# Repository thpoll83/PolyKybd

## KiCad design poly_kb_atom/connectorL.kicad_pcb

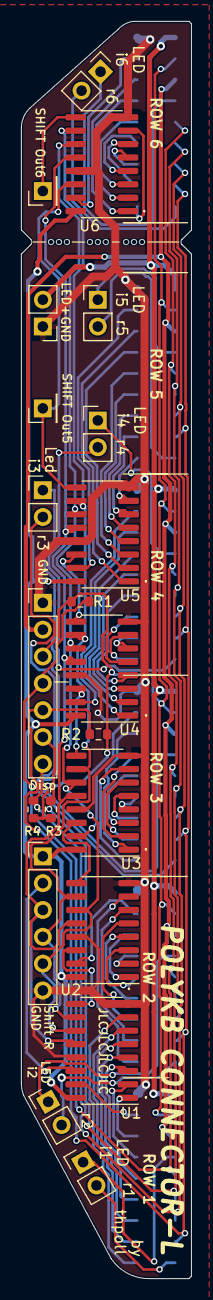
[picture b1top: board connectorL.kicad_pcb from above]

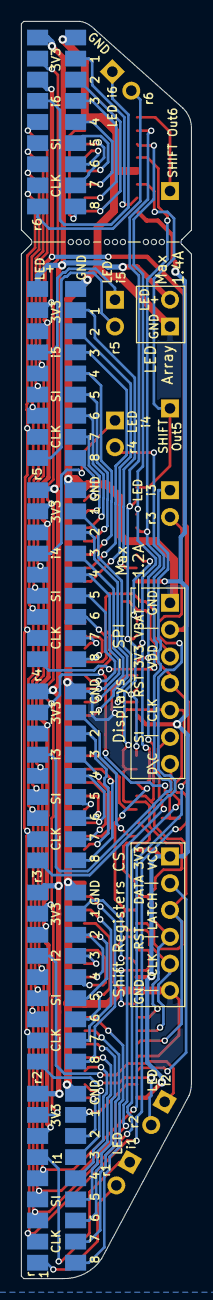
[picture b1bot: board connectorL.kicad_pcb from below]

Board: 2 copper layers, 16.1 x 119.0 mm, 36 parts (12 on the bottom side), 79 nets.

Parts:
J1, J2, J3, J4, J5, J6, J7, J8, J9, J10, J11, J12: Conn_01x09; AtomConnect2
J13: Conn_01x07; PinHeader_1x07_P2.54mm_Vertical
J14: Conn_01x06; PinHeader_1x06_P2.54mm_Vertical
J15, J17: Conn_01x01; PinHeader_1x01_P2.54mm_Vertical
J16, J21, J22, J23, J24, J25, J26: Conn_01x02; PinHeader_1x02_P2.54mm_Vertical
R1, R2, R3, R4: 1M; R_0603_1608Metric
U1, U2, U3, U4, U5, U6: 74HCT595; SOIC-16_3.9x9.9mm_P1.27mm
mouse-bite-2mm-slot, mouse-bite-2mm-slot#2, mouse-bite-2mm-slot#3: VAL**; mouse-bite-3x

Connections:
1: J1.2, U1.15
2: J1.3, U1.1
3: J1.4, U1.2
4: J1.5, U1.3
5: J1.6, U1.4
6: J1.7, U1.5
7: J1.8, U1.6
8: J1.9, U1.7
9: J3.2, U2.15
10: J3.3, U2.1
11: J3.4, U2.2
12: J3.5, U2.3
13: J3.6, U2.4
14: J3.7, U2.5
15: J3.8, U2.6
16: J3.9, U2.7
17: J5.2, U3.15
18: J5.3, U3.1
19: J5.4, U3.2
20: J5.5, U3.3
21: J5.6, U3.4
22: J5.7, U3.5
23: J5.8, U3.6
24: J5.9, U3.7
25: J7.2, U4.15
26: J7.3, U4.1
27: J7.4, U4.2
28: J7.5, U4.3
29: J7.6, U4.4
30: J7.7, U4.5
31: J7.8, U4.6
32: J7.9, U4.7
33: J9.2, U5.15
34: J9.3, U5.1
35: J9.4, U5.2
36: J9.5, U5.3
37: J9.6, U5.4
38: J9.7, U5.5
39: J9.8, U5.6
40: J9.9, U5.7
41: J11.2, U6.15
42: J11.3, U6.1
43: J11.4, U6.2
44: J11.5, U6.3
45: J11.6, U6.4
46: J11.7, U6.5
47: J11.8, U6.6
48: J11.9, U6.7
+3V3: J14.1, U1.16, U2.16, U3.16, U4.16, U5.16, U6.16
CLK: J2.8, J4.8, J6.8, J8.8, J10.8, J12.8, J13.5, R2.2
D\C: J2.7, J4.7, J6.7, J8.7, J10.7, J12.7, J13.7, R4.2
GND: J1.1, J3.1, J5.1, J7.1, J9.1, J11.1, J13.1, J14.6, J16.1, U1.8, U1.13, U2.8, U2.13, U3.8, U3.13, U4.8, U4.13, U5.8, U5.13, U6.8, U6.13
LedIn1: J2.4, J21.1
LedIn2: J4.4, J22.1
LedIn3: J6.4, J23.1
LedIn4: J8.4, J24.1
LedIn5: J10.4, J25.1
LedIn6: J12.4, J26.1
unnamed: U1.9, U2.14
unnamed: U2.9, U3.14
unnamed: U3.9, U4.14
unnamed: U4.9, U5.14
RST: J2.5, J4.5, J6.5, J8.5, J10.5, J12.5, J13.4, R1.2
SHIFTR_AOUT: J17.1, U5.9, U6.14
SHIFTR_CLK: J14.5, U1.11, U2.11, U3.11, U4.11, U5.11, U6.11
SHIFTR_DATA: J14.2, U1.14
SHIFTR_LATCH_CLK: J14.3, U1.12, U2.12, U3.12, U4.12, U5.12, U6.12
SHIFTR_OUT: J15.1, U6.9
SHIFTR_RST: J14.4, U1.10, U2.10, U3.10, U4.10, U5.10, U6.10
SI: J2.6, J4.6, J6.6, J8.6, J10.6, J12.6, J13.6, R3.2
VBAT: J2.3, J4.3, J6.3, J8.3, J10.3, J12.3, J13.2
VDD_3V3: J2.2, J4.2, J6.2, J8.2, J10.2, J12.2, J13.3, R1.1, R2.1, R3.1, R4.1
VLED: J2.1, J4.1, J6.1, J8.1, J10.1, J12.1, J16.2
r1: J2.9, J21.2
r2: J4.9, J22.2
r3: J6.9, J23.2
r4: J8.9, J24.2
r5: J10.9, J25.2
r6: J12.9, J26.2

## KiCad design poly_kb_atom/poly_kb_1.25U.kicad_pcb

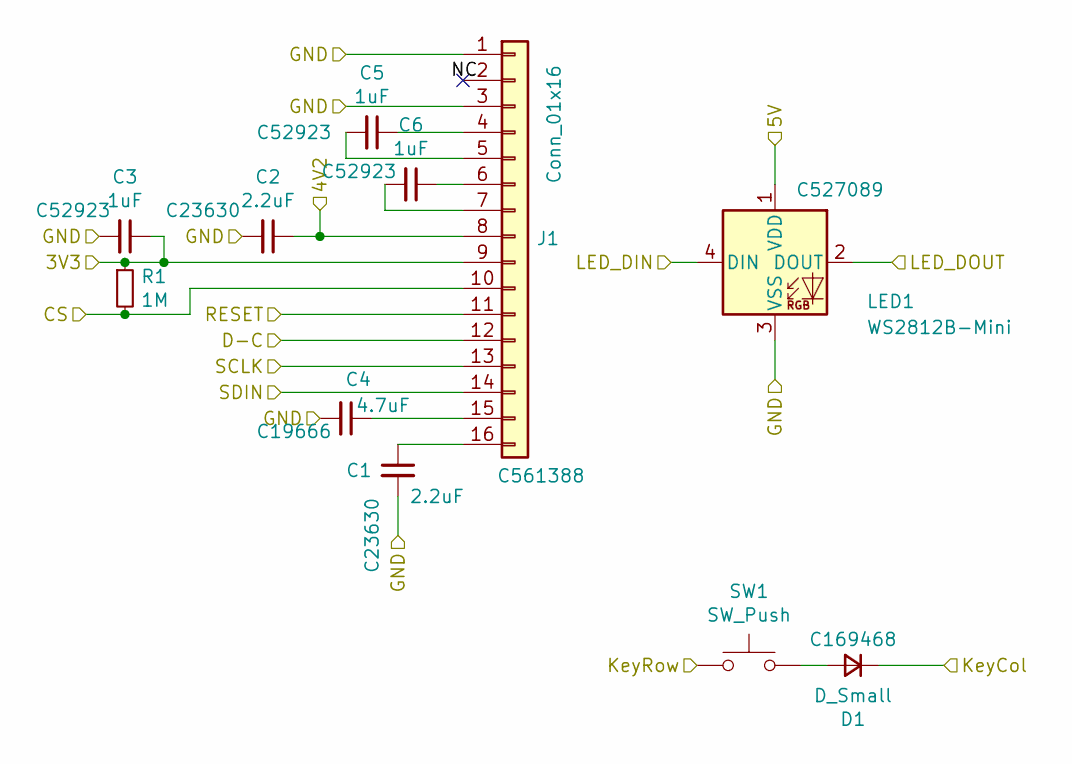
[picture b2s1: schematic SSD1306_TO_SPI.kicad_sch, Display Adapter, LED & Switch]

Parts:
C1, C2: 2.2uF; C_0603_1608Metric; LCSC C23630
C3, C5, C6: 1uF; C_0402_1005Metric; LCSC C52923
C4: 4.7uF; C_0603_1608Metric; LCSC C19666
D1: D_Small; D_SOD-323; LCSC C169468
J1: Conn_01x16; FPC_16_JUSHUO_AFC05_S16FIA_00; LCSC C561388
LED1: WS2812B-Mini; LCSC C527089
R1: 1M; R_0402_1005Metric
SW1: SW_Push; SW_Cherry_MX_1.00u_PCB_NoSilk

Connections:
/Keyboard/sheet605ED2EB/3V3: C3.1, J1.9, R1.1; also elsewhere on the board
/Keyboard/sheet605ED2EB/4V2: C2.1, J1.8; also elsewhere on the board
/Keyboard/sheet605ED2EB/5V: LED1.1 (VDD); also elsewhere on the board
/Keyboard/sheet605ED2EB/CS: J1.10, R1.2; also elsewhere on the board
/Keyboard/sheet605ED2EB/D-C: J1.12; also elsewhere on the board
/Keyboard/sheet605ED2EB/GND: C1.2, C2.2, C3.2, C4.2, J1.1, J1.3, LED1.3 (VSS); also elsewhere on the board
/Keyboard/sheet605ED2EB/KeyCol: D1.1 (K); also elsewhere on the board
/Keyboard/sheet605ED2EB/KeyRow: SW1.1; also elsewhere on the board
/Keyboard/sheet605ED2EB/LED_DIN: LED1.2 (DOUT), LED1.4 (DIN); also elsewhere on the board
/Keyboard/sheet605ED2EB/RESET: J1.11; also elsewhere on the board
/Keyboard/sheet605ED2EB/SCLK: J1.13; also elsewhere on the board
/Keyboard/sheet605ED2EB/SDIN: J1.14; also elsewhere on the board
unnamed: C1.1, J1.16
unnamed: C4.1, J1.15
unnamed: C5.1, J1.4
unnamed: C5.2, J1.5
unnamed: C6.1, J1.6
unnamed: C6.2, J1.7
unnamed: D1.2 (A), SW1.2

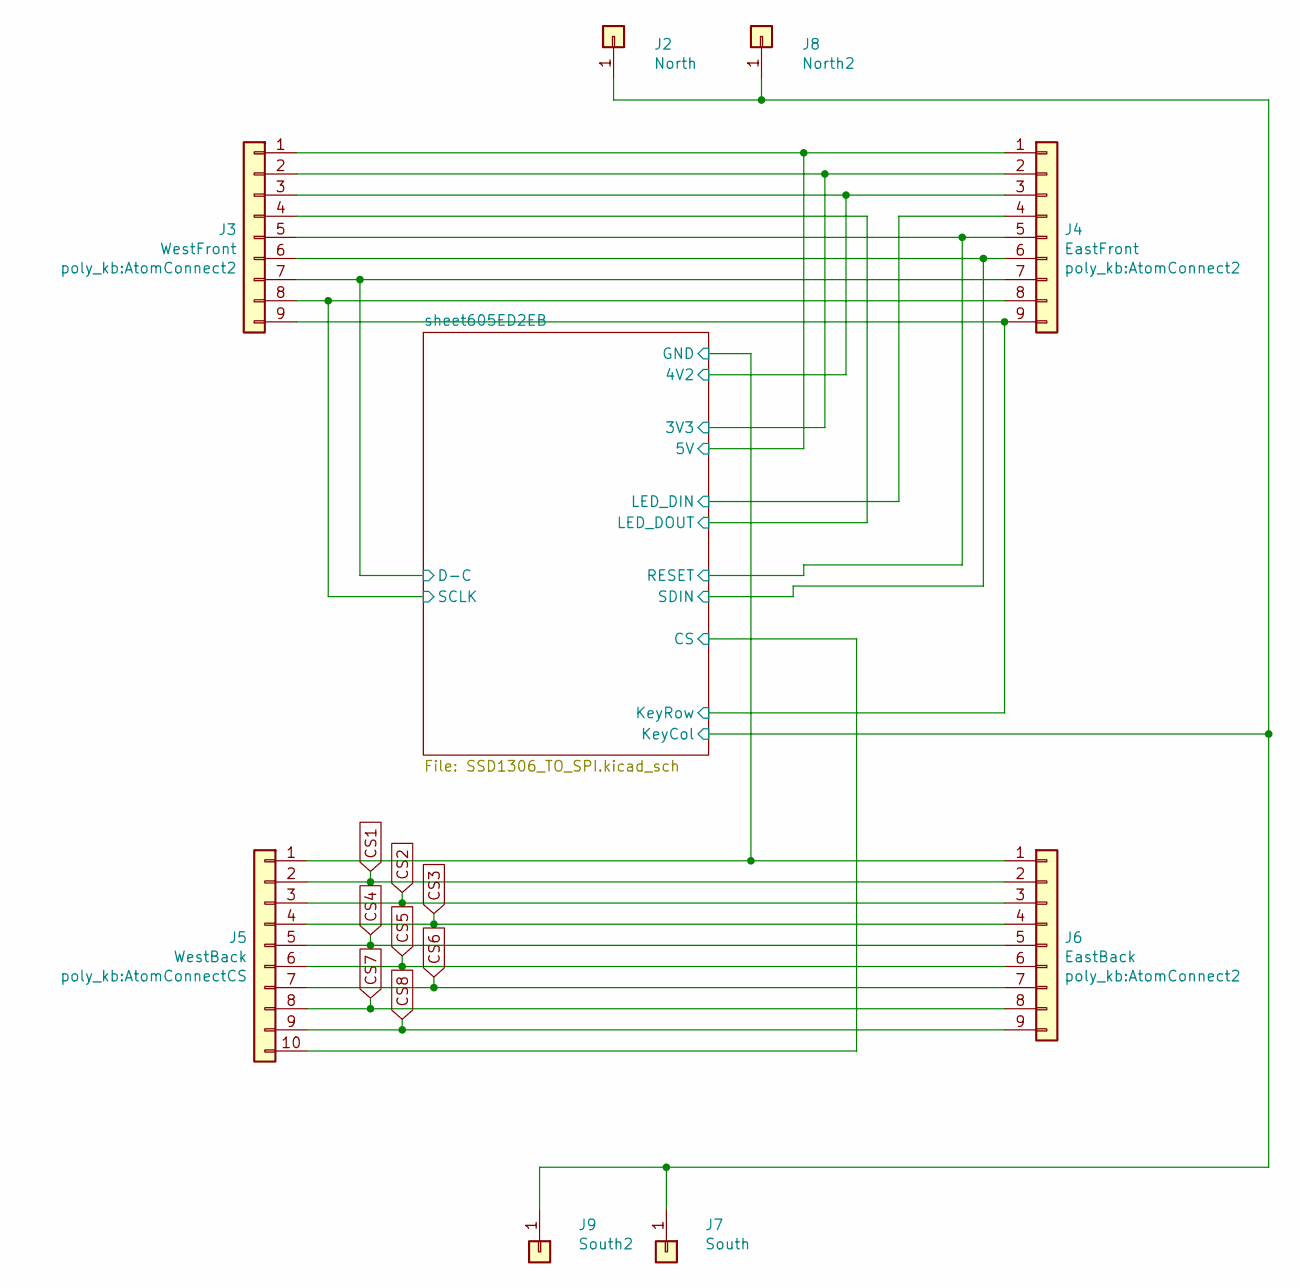
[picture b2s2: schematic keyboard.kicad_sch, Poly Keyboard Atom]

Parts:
J2: North; TestPoin_1.5x1.5mm_Drill0.7mm
J3: WestFront; AtomConnect2
J4: EastFront; AtomConnect2
J5: WestBack; AtomConnectCS
J6: EastBack; AtomConnect2
J7: South; TestPoin_1.5x1.5mm_Drill0.7mm
J8: North2; TestPoin_1.5x1.5mm_Drill0.7mm
J9: South2; TestPoin_1.5x1.5mm_Drill0.7mm

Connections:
/Keyboard/sheet605ED2EB/3V3: J3.2, J4.2; also elsewhere on the board
/Keyboard/sheet605ED2EB/4V2: J3.3, J4.3; also elsewhere on the board
/Keyboard/sheet605ED2EB/5V: J3.1, J4.1; also elsewhere on the board
/Keyboard/sheet605ED2EB/CS: J5.10; also elsewhere on the board
/Keyboard/sheet605ED2EB/D-C: J3.7, J4.7; also elsewhere on the board
/Keyboard/sheet605ED2EB/GND: J5.1, J6.1; also elsewhere on the board
/Keyboard/sheet605ED2EB/KeyCol: J2.1, J7.1, J8.1, J9.1; also elsewhere on the board
/Keyboard/sheet605ED2EB/KeyRow: J3.9, J4.9; also elsewhere on the board
/Keyboard/sheet605ED2EB/LED_DIN: J3.4, J4.4; also elsewhere on the board
/Keyboard/sheet605ED2EB/RESET: J3.5, J4.5; also elsewhere on the board
/Keyboard/sheet605ED2EB/SCLK: J3.8, J4.8; also elsewhere on the board
/Keyboard/sheet605ED2EB/SDIN: J3.6, J4.6; also elsewhere on the board
CS1: J5.2, J6.2
CS2: J5.3, J6.3
CS3: J5.4, J6.4
CS4: J5.5, J6.5
CS5: J5.6, J6.6
CS6: J5.7, J6.7
CS7: J5.8, J6.8
CS8: J5.9, J6.9

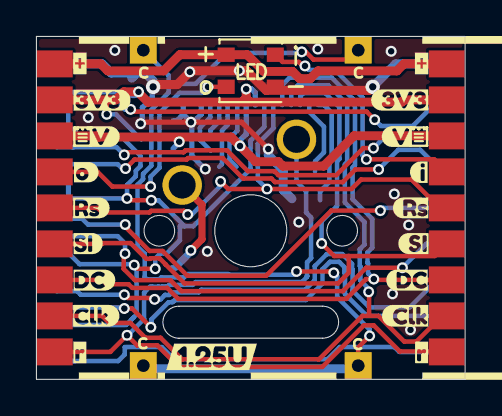
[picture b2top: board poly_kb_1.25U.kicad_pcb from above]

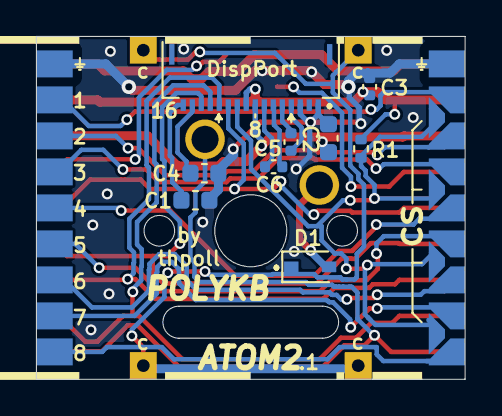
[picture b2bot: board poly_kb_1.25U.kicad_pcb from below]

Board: 2 copper layers, 23.8 x 19.0 mm, 38 parts (11 on the bottom side), 27 nets.

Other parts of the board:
kibuzzard-61EFA8F1: G***; kibuzzard-61EFA8F1
kibuzzard-61EFAA6D: G***; kibuzzard-61EFAA6D
kibuzzard-61EFABBF: G***; kibuzzard-61EFABBF
kibuzzard-61EFACF9: G***; kibuzzard-61EFACF9
kibuzzard-61EFBE2C: G***; kibuzzard-61EFBE2C
kibuzzard-61EFBE3D: G***; kibuzzard-61EFBE3D
kibuzzard-61EFBE21: G***; kibuzzard-61EFBE21
kibuzzard-61EFBE87: G***; kibuzzard-61EFBE87
kibuzzard-61EFD7F9: G***; kibuzzard-61EFD7F9
kibuzzard-61EFD863: G***; kibuzzard-61EFD863
kibuzzard-61EFD879: G***; kibuzzard-61EFD879
kibuzzard-61EFD908, kibuzzard-61EFD908#2: G***; kibuzzard-61EFD908
kibuzzard-61EFD947, kibuzzard-61EFD947#2: G***; kibuzzard-61EFD947
kibuzzard-61EFDAA0: G***; kibuzzard-61EFDAA0
kibuzzard-61EFDAC6: G***; kibuzzard-61EFDAC6
kibuzzard-61EFDAEE: G***; kibuzzard-61EFDAEE
kibuzzard-6209FD7E: G***; kibuzzard-6209FD7E

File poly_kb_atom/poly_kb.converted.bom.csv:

Designator,Quantity,Value,Footprint,LCSC Part #,Comment
"C1, C2",2,2.2uF,C_0603_1608Metric,C23630," Unpolarized capacitor, small symbol"
"C3, C5, C6",3,1uF,C_0402_1005Metric,C52923," Unpolarized capacitor, small symbol"
C4,1,4.7uF,C_0603_1608Metric,C19666," Unpolarized capacitor, small symbol"
D1,1,D_Small,D_SOD-323F,C2826370," Diode, small symbol"
J1,1,Conn_01x16,FPC_16_JUSHUO_AFC05_S16FIA_00,C561388," Generic connector, single row, 01x16, script generated (kicad-library-utils/schlib/autogen/connector/)"
J2,1,North,TestPoin_1.5x1.5mm_Drill0.7mm,," Generic connector, single row, 01x01, script generated (kicad-library-utils/schlib/autogen/connector/)"
J3,1,WestFront,AtomConnect2,," Generic connector, single row, 01x09, script generated (kicad-library-utils/schlib/autogen/connector/)"
J4,1,EastFront,AtomConnect2,," Generic connector, single row, 01x09, script generated (kicad-library-utils/schlib/autogen/connector/)"
J5,1,WestBack,AtomConnectCS,," Generic connector, single row, 01x10, script generated (kicad-library-utils/schlib/autogen/connector/)"
J6,1,EastBack,AtomConnect2,," Generic connector, single row, 01x09, script generated (kicad-library-utils/schlib/autogen/connector/)"
J7,1,South,TestPoin_1.5x1.5mm_Drill0.7mm,," Generic connector, single row, 01x01, script generated (kicad-library-utils/schlib/autogen/connector/)"
J8,1,North2,TestPoin_1.5x1.5mm_Drill0.7mm,," Generic connector, single row, 01x01, script generated (kicad-library-utils/schlib/autogen/connector/)"
J9,1,South2,TestPoin_1.5x1.5mm_Drill0.7mm,," Generic connector, single row, 01x01, script generated (kicad-library-utils/schlib/autogen/connector/)"
LED1,1,WS2812B-Mini,WS2812B-Mini,C527089, RGB LED with integrated controller
SW1,1,SW_Push,SW_Cherry_MX_1.00u_PCB_NoSilk,," Push button switch, generic, two pins"
